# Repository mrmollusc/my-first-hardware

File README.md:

# my-first-hardware (Heartbie)

The heartbie device is a small companion toy that is a spin-off of the [starbie](https://github.com/SharKingStudios/Starbie) starter project provided by [Half Life](https://halflife.hackclub.com/) for the week 1 starter project. The heartbie has the components of the starbie; namely microcontroller, OLED display which is for visual response to the heartbie's environment, environment sensor, movement sensor and keys for user interaction. However, the heartbie features an additional speaker and also customizes the keys and PCB layout.

## Layout

## Features

- **Firmware:** Arduino C
- **PCB:** JLCPCB service
- **Microcontroller:** XIAO ESP32 C3 Mini
- **Display:** 128x64 OLED Display
- **Environment Sensor:** DHT 11
- **Movement Sensor:** MPU 6050
- **Key Switches:** Outemu Silent Switches
- **Key Caps:** Generic Transparent
- **Speaker:** Generic 36mm
- **Speaker Chip:** MAX98357A

## Grant-funded ($30 tier 1)

| Item | Purpose | Qty | Unit (USD) | Total (USD) | Link |
|---|---|---|---|---|---|
| Heartbie PCB 2-layer84x84mm | Custom Heart Shaped Board | 5 | 0.80 | 4.00 | [JLCPCB](https://jlcpcb.com/quote) |
| JLCPCB shipping (Global Standard Direct Line → AU) | Shipping | 1 | 7.56 | 7.56 | [JLCPCB](https://jlcpcb.com/quote) |
| Seeed Studio XIAO ESP32-C3 | Microcontroller | 1 | 7.56 | 7.56 | [AliExpress](https://www.aliexpress.com/item/1005008304166336.html) |
| 0.96in 128x64 I2C OLED (SSD1306) | OLED Display | 1 | 1.06 | 1.06 | [AliExpress](https://www.aliexpress.com/item/1005006262908701.html) |
| DHT 11 Sensor | Environment sensor | 1 | 1.54 | 1.54 | [AliExpress](https://www.aliexpress.com/item/1005008818897051.html) |
| MPU 6050 Sensor | Movement sensor | 1 | 4.45 | 4.45 | [AliExpress](https://www.aliexpress.com/item/1005008604349573.html) |
| Outemu Silent Switches (10pcs) | Key Switches | 2 | 0.35 | 0.70 | [AliExpress](https://www.aliexpress.com/item/1005006905361113.html) |
| Clear Keycap (4pcs) | Keycap | 2 | 0.95 | 1.90 | [AliExpress](https://www.aliexpress.com/item/1005013363777380.html) |
| Speaker 36mm | Sound | 1 | 0.85 | 0.85 | [AliExpress](https://www.aliexpress.com/item/1005009194030447.html) |
| MAX98357A | Sound Amplifier Chip | 1 | 1.92 | 1.92 | [AliExpress](https://www.aliexpress.com/item/1005012452360614.html) |
| **Grant total** | | | | **31.34** | |

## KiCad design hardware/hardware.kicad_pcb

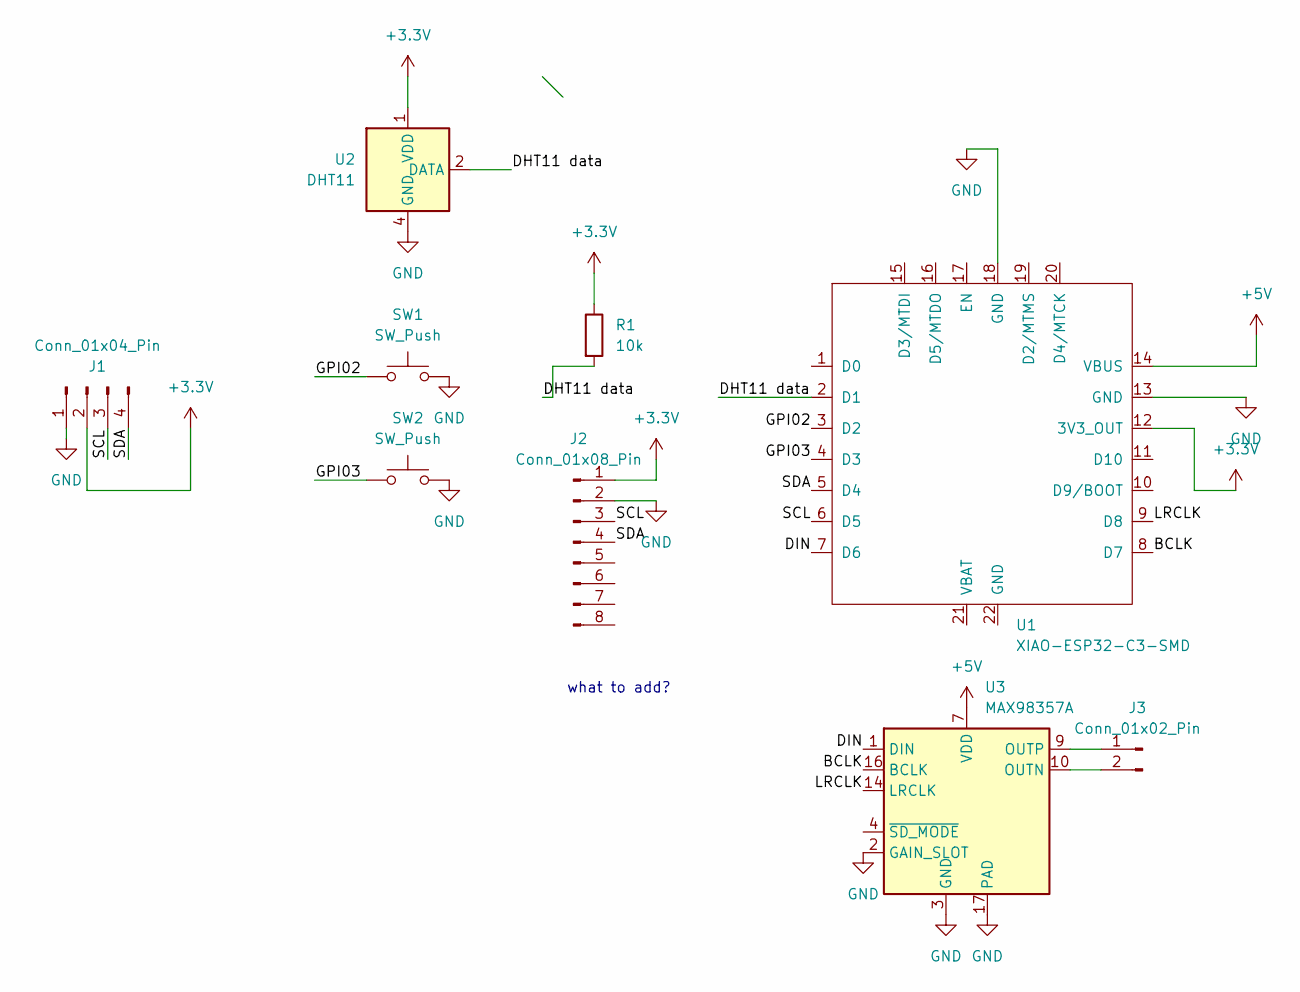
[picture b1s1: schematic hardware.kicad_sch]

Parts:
J1: Conn_01x04_Pin; Display_128x64_096_I2C
J2: Conn_01x08_Pin; PinHeader_1x08_P2.54mm_Vertical
J3: Conn_01x02_Pin; PinHeader_1x02_P1.00mm_Vertical
R1: 10k; R_Axial_DIN0204_L3.6mm_D1.6mm_P7.62mm_Horizontal
SW1, SW2: SW_Push; SW_Cherry_MX_1.00u_PCB
U1: XIAO-ESP32-C3-SMD
U2: DHT11; Aosong_DHT11_5.5x12.0_P2.54mm
U3: MAX98357A; TQFN-16-1EP_3x3mm_P0.5mm_EP1.23x1.23mm

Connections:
+3.3V: J1.2, J2.1, R1.1, U1.12 (3V3_OUT), U2.1 (VDD)
+5V: U1.14 (VBUS), U3.7 (VDD), U3.8 (VDD)
/BCLK: U1.8 (D7), U3.16 (BCLK)
/DHT11 data: R1.2, U1.2 (D1), U2.2 (DATA)
/DIN: U1.7 (D6), U3.1 (DIN)
/GPI02: SW1.1, U1.3 (D2)
/GPI03: SW2.1, U1.4 (D3)
/LRCLK: U1.9 (D8), U3.14 (LRCLK)
/SCL: J1.3, J2.3, U1.6 (D5)
/SDA: J1.4, J2.4, U1.5 (D4)
GND: J1.1, J2.2, SW1.2, SW2.2, U1.13 (GND), U1.18 (GND), U2.4 (GND), U3.2 (GAIN_SLOT), U3.3 (GND), U3.11 (GND), U3.15 (GND), U3.17 (PAD)
unnamed: J3.1, U3.9 (OUTP)
unnamed: J3.2, U3.10 (OUTN)

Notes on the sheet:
what to add?

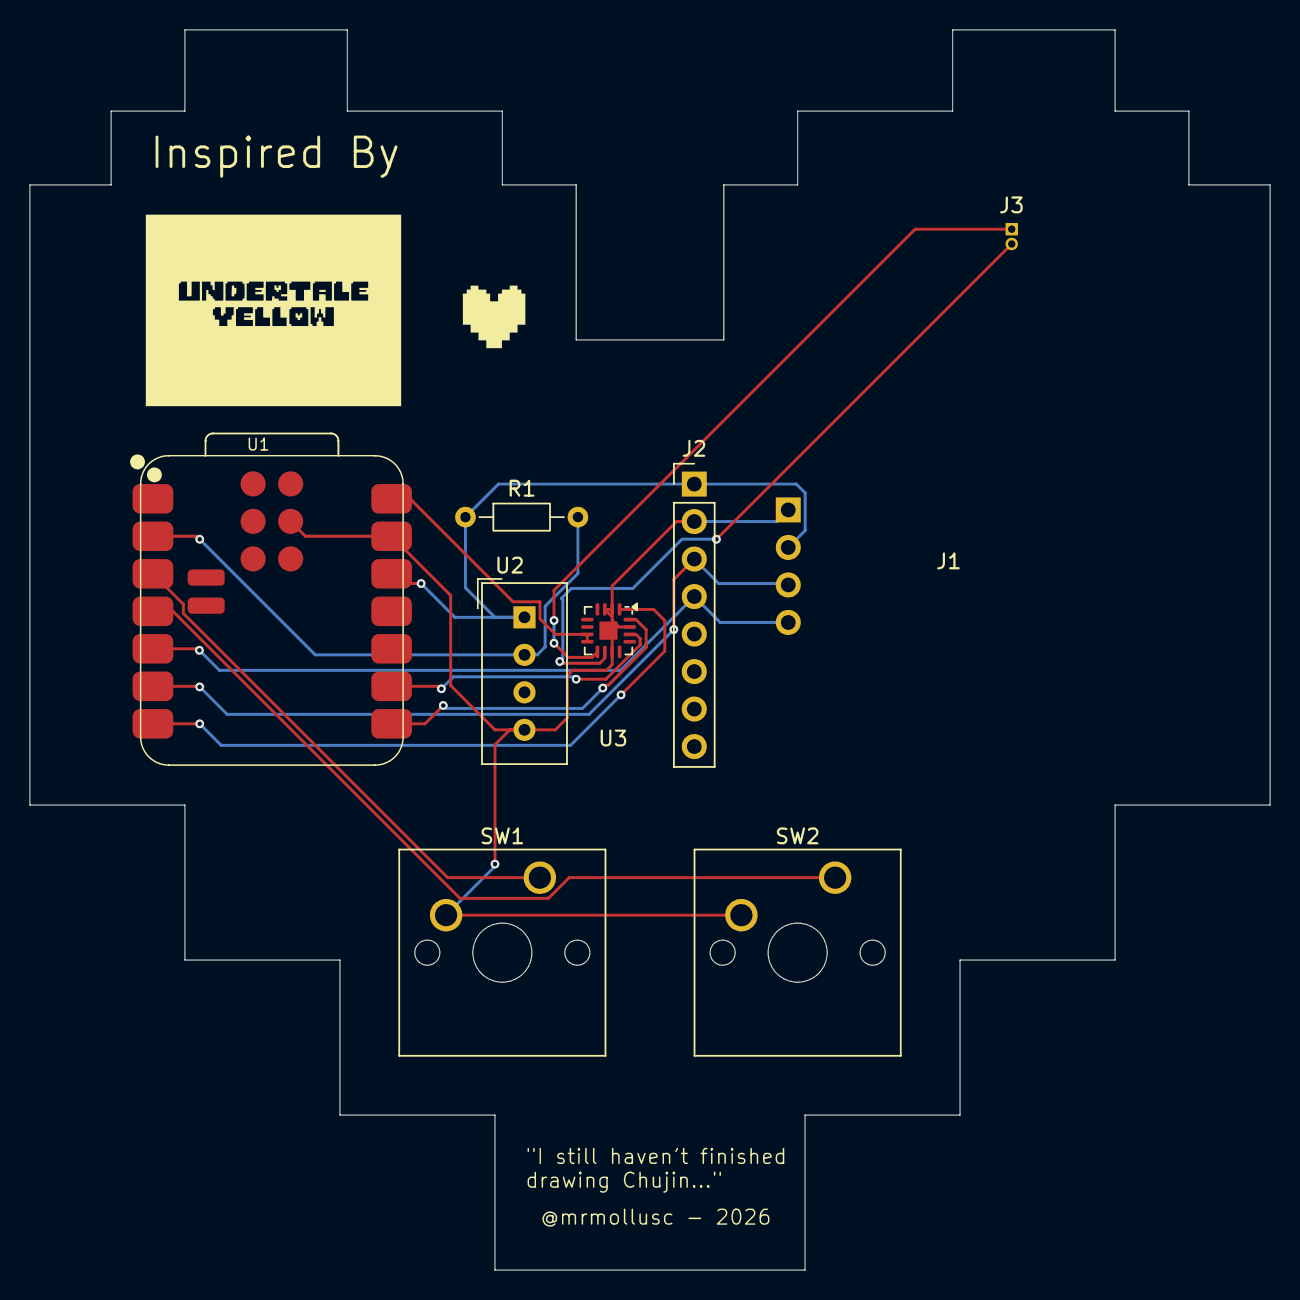
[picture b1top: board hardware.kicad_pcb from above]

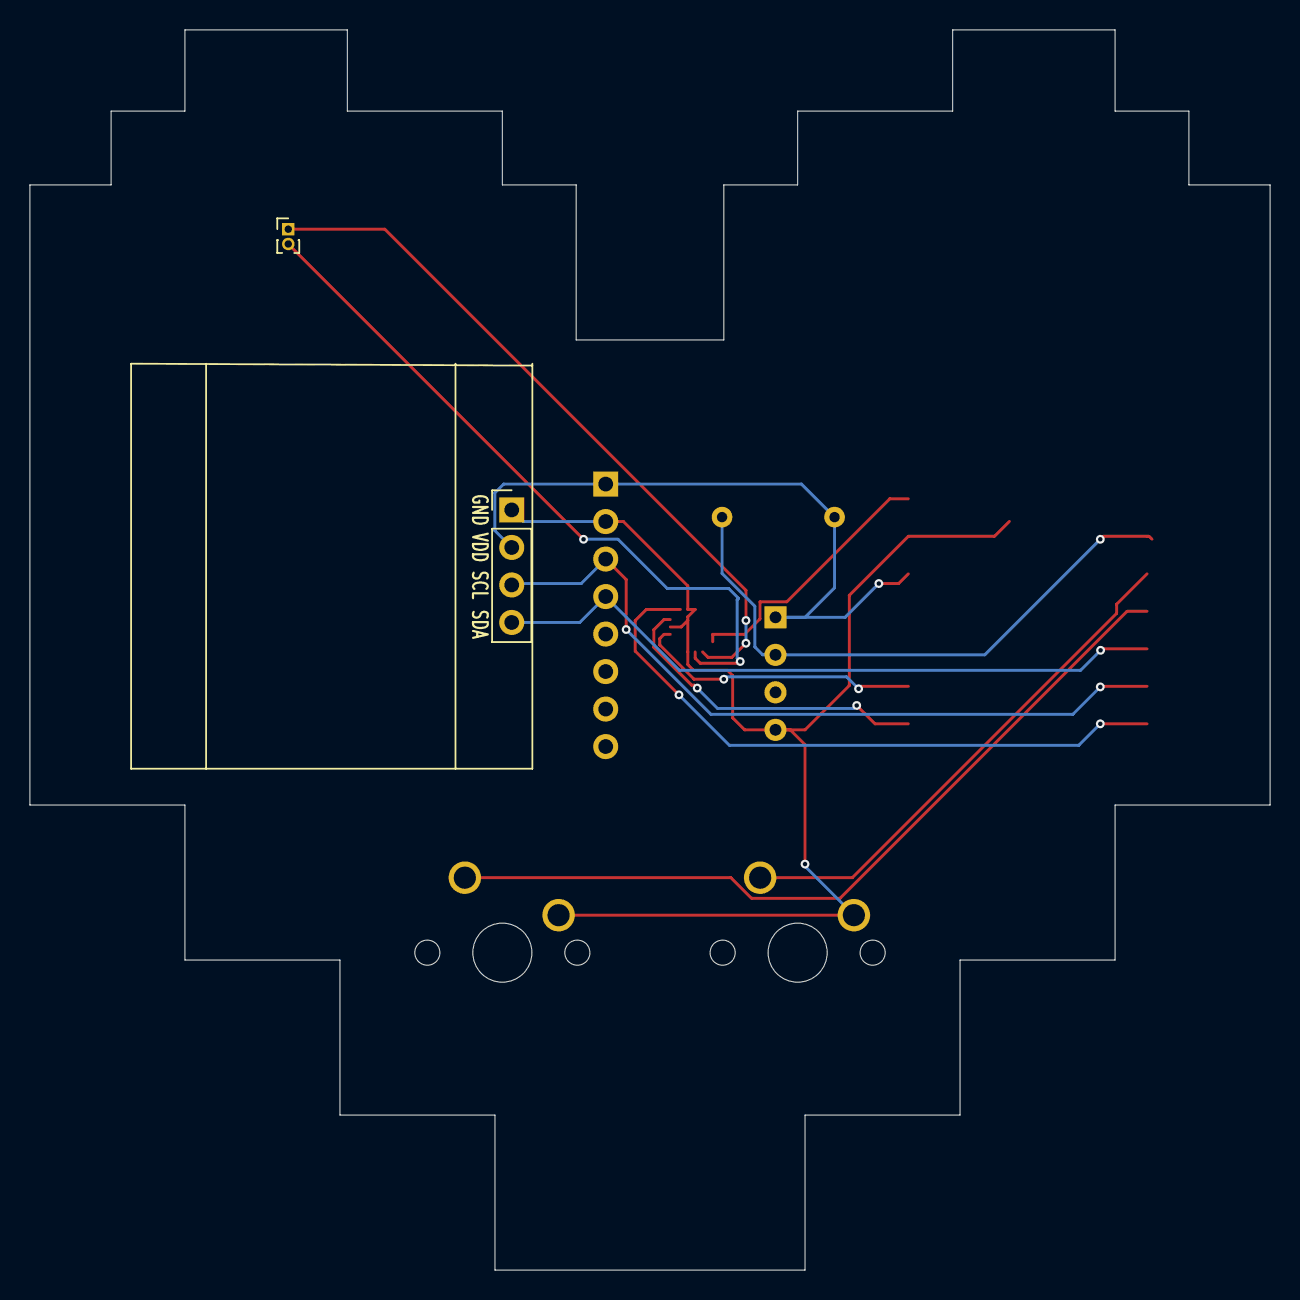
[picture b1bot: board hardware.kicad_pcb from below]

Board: 2 copper layers, 84.0 x 84.0 mm, 9 parts (2 on the bottom side), 13 nets.
